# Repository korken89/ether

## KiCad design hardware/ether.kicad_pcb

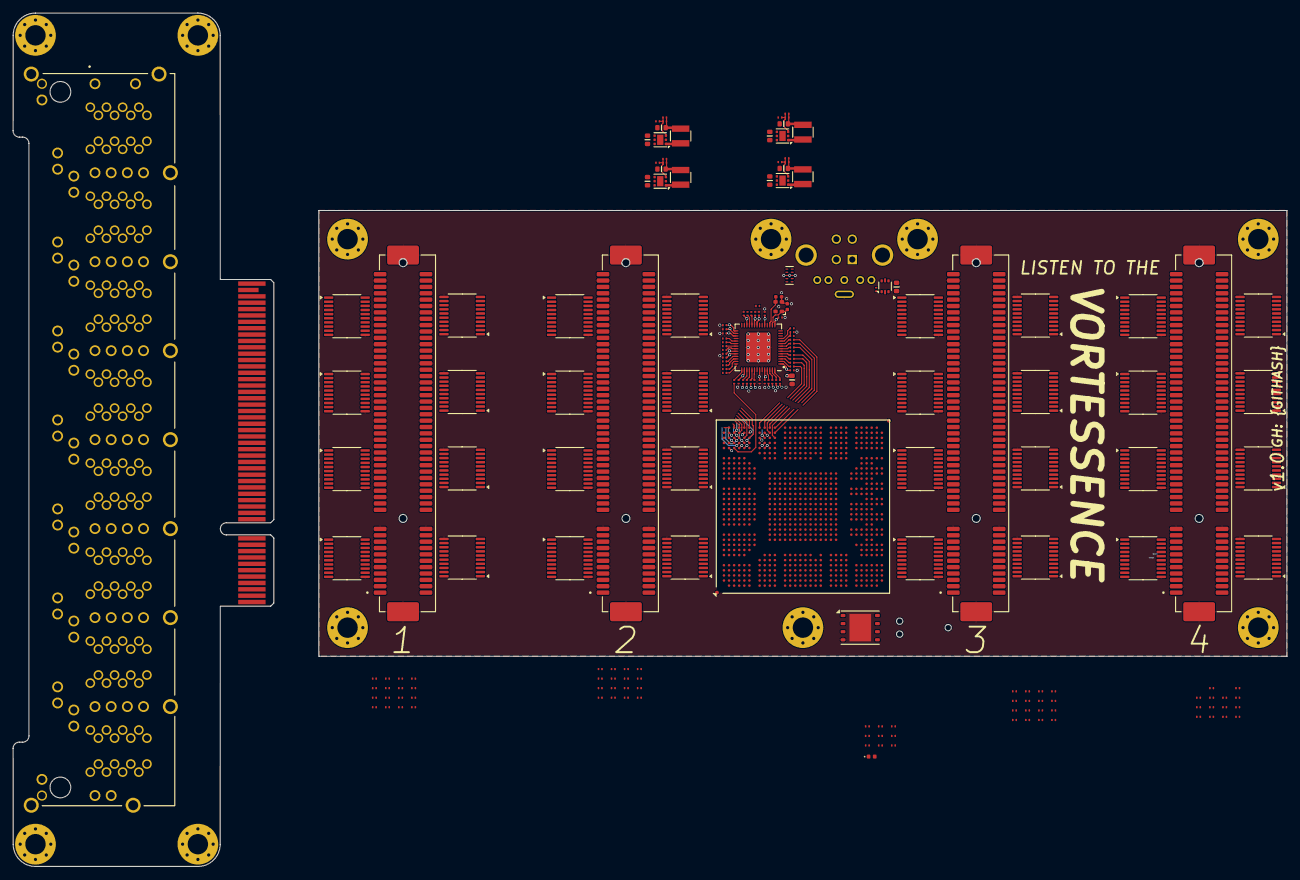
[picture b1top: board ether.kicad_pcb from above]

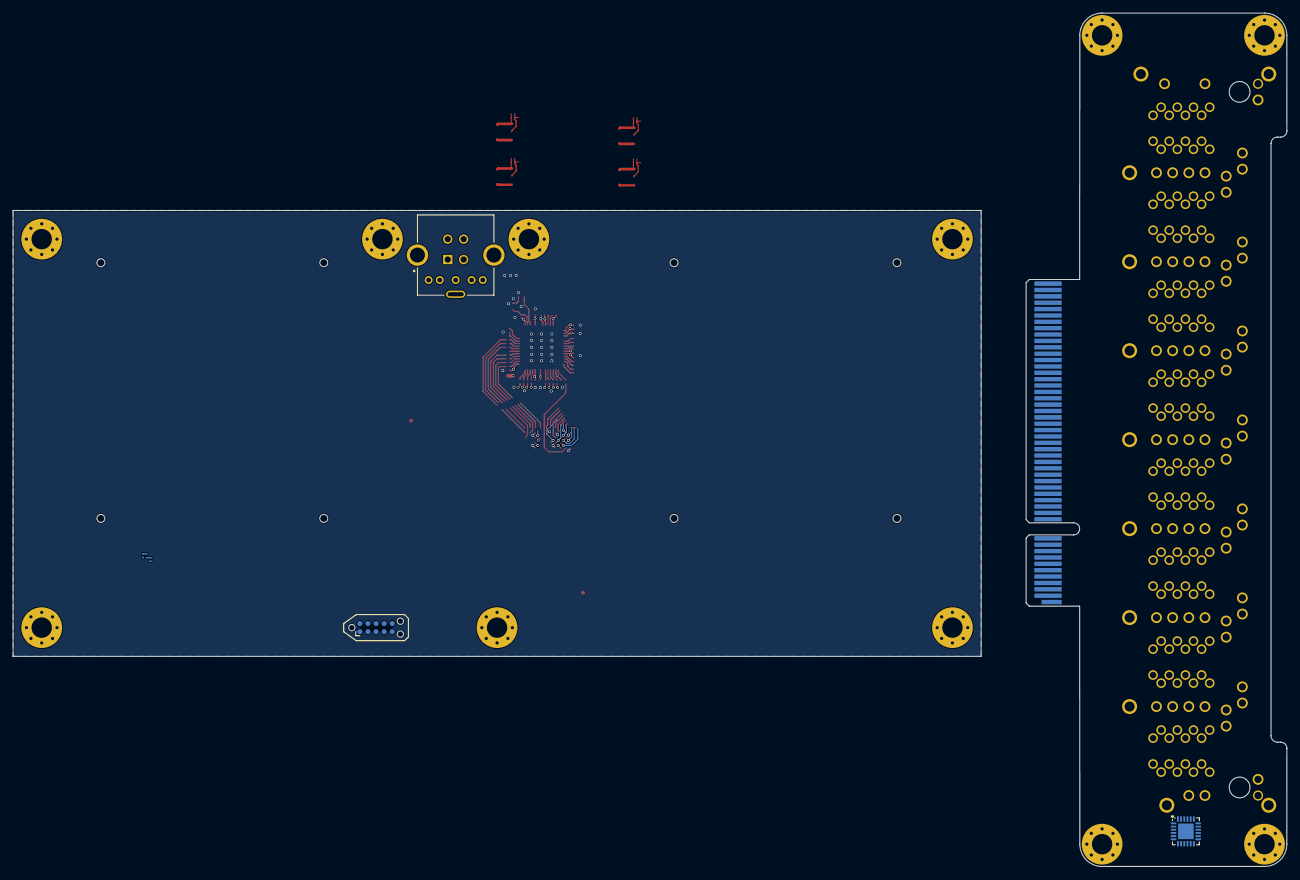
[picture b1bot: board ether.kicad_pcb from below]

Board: 6 copper layers, 200.0 x 134.0 mm, 205 parts (5 on the bottom side), 373 nets.

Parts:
C101, C102, C103, C104, C105, C106, C107, C108, C109, C110, C111, C112, C113, C114, C117, C118, C119, C120, C122, C301, C302, C303, C304, C305, C306, C307, C308, C309, C310, C311, C312, C313, C314, C315, C316, C401, C402, C403, C404, C405, C406, C407, C408, C409, C410, C411, C412, C413, C414, C415, C416, C501, C502, C503, C504, C505, C506, C507, C508, C509, C510, C511, C512, C513, C514, C515, C516, C601, C602, C603, C604, C605, C606, C607, C608, C609, C610, C611, C612, C613, C614, C615, C616: 0.1u; C_0201
C115, C116: 10p; C_0402
C121, C201, C202, C203, C204: 4.7u; C_0603
C206, C207, C208, C209: 22p; C_0201
C211, C212, C213, C214: 22u; C_0603
D101: LED_Small; LED_0402_1005Metric
FB101: FerriteBead_Small; R_0603
H101, H102, H103, H104, H105, H106, H107: MountingHole_Pad; MountingHole_3.2mm_M3_Pad_Via
J101: TC2050; Tag-Connect_TC2050-IDC-NL_2x05_P1.27mm_Vertical
J102: GSB422137EU; AMPHENOL_GSB422137EU
J301, J401, J501, J601: 10061913-102PLF; AMPHENOL_10061913-102PLF
J301#2: SS-74500-022; BEL_SS-74500-022
L201, L202, L203, L204: 2.2u; L_Abracon_ASPI-3012S
R101: 1.6k; R_0201
R102, R103, R104, R133, R136: 10k; R_0201
R105, R106, R107, R108, R109, R110, R111, R112, R113, R114, R115, R116, R117, R118, R119, R120, R121, R122, R123, R124, R125, R126, R127, R128: 33; R_0201
R129, R130, R131, R132, R134: 1k; R_0201
R135: 0; R_0201
R201, R202, R203, R204, R205, R206, R207, R208: R_0201
U101: ECP5U_85_CABGA756; Lattice_caBGA-756_27.0x27.0mm_Layout32x32_P0.8mm
U102: PUSB3FR4Z; DFN-10-1.0x2.5mm_P0.5mm
U103: FT600Q; QFN-56-1EP_7x7mm_P0.4mm_EP5.7x5.7mm_FT600
U104: TCA9535RTWR; WQFN-24-1EP_4x4mm_P0.5mm_EP2.45x2.45mm
U105: W25Q128JVP; WSON-8-1EP_6x5mm_P1.27mm_EP3.4x4.3mm
U108: USBLC6-2P6; SOT-666
U201, U202, U203, U204: TPS62290; WSON-6-1EP_2x2mm_P0.65mm_EP1x1.6mm
U301, U303, U305, U307, U309, U310, U311, U312, U401, U403, U405, U407, U409, U410, U411, U412, U501, U503, U505, U507, U509, U510, U511, U512, U601, U603, U605, U607, U609, U610, U611, U612: TXB0108DQSR; TSSOP-20_4.4x6.5mm_P0.65mm
Y101: 30 MHz; Crystal_4Pin_2.0x1.6mm

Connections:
+1V1: C206.2, C211.1, L201.2, R201.2, U101.AA12 (VCC[36]), U101.AA13 (VCC[36]), U101.AA14 (VCC[36]), U101.AA15 (VCC[36]), U101.AA16 (VCC[36]), U101.AA17 (VCC[36]), U101.AA18 (VCC[36]), U101.AA19 (VCC[36]), U101.AA20 (VCC[36]), U101.AA21 (VCC[36]), U101.M12 (VCC[36]), U101.M13 (VCC[36]), U101.M14 (VCC[36]), U101.M15 (VCC[36]), U101.M16 (VCC[36]), U101.M17 (VCC[36]), U101.M18 (VCC[36]), U101.M19 (VCC[36]), U101.M20 (VCC[36]), U101.M21 (VCC[36]), U101.N12 (VCC[36]), U101.N21 (VCC[36]), U101.P12 (VCC[36]), U101.P21 (VCC[36]), U101.R12 (VCC[36]), U101.R21 (VCC[36]), U101.T12 (VCC[36]), U101.T21 (VCC[36]), U101.U12 (VCC[36]), U101.U21 (VCC[36]), U101.V12 (VCC[36]), U101.V21 (VCC[36]), U101.W12 (VCC[36]), U101.W21 (VCC[36]), U101.Y12 (VCC[36]), U101.Y21 (VCC[36])
+1V5: C301.1, C302.1, C303.1, C304.1, C305.1, C306.1, C307.1, C308.1, C401.1, C402.1, C403.1, C404.1, C405.1, C406.1, C407.1, C408.1, C501.1, C502.1, C503.1, C504.1, C505.1, C506.1, C507.1, C508.1, C601.1, C602.1, C603.1, C604.1, C605.1, C606.1, C607.1, C608.1, U301.2 (V_{CCA}), U303.2 (V_{CCA}), U305.2 (V_{CCA}), U307.2 (V_{CCA}), U309.2 (V_{CCA}), U310.2 (V_{CCA}), U311.2 (V_{CCA}), U312.2 (V_{CCA}), U401.2 (V_{CCA}), U403.2 (V_{CCA}), U405.2 (V_{CCA}), U407.2 (V_{CCA}), U409.2 (V_{CCA}), U410.2 (V_{CCA}), U411.2 (V_{CCA}), U412.2 (V_{CCA}), U501.2 (V_{CCA}), U503.2 (V_{CCA}), U505.2 (V_{CCA}), U507.2 (V_{CCA}), U509.2 (V_{CCA}), U510.2 (V_{CCA}), U511.2 (V_{CCA}), U512.2 (V_{CCA}), U601.2 (V_{CCA}), U603.2 (V_{CCA}), U605.2 (V_{CCA}), U607.2 (V_{CCA}), U609.2 (V_{CCA}), U610.2 (V_{CCA}), U611.2 (V_{CCA}), U612.2 (V_{CCA})
+2V5: C208.2, C213.1, L203.2, R205.2, U101.AC11 (VCCAUX[8]), U101.AC22 (VCCAUX[8]), U101.K13 (VCCAUX[8]), U101.K20 (VCCAUX[8]), U101.N10 (VCCAUX[8]), U101.N23 (VCCAUX[8]), U101.Y10 (VCCAUX[8]), U101.Y23 (VCCAUX[8])
+3V3: C102.1, C103.1, C105.1, C109.1, C112.1, C113.1, C119.1, C122.1, C209.2, C214.1, J101.1, J301.B48, J401.B48, J501.B48, J601.B48, L204.2, R102.1, R103.1, R104.1, R129.1, R130.1, R131.1, R132.1, R133.1, R136.1, R207.2, U101.D28 (PR11B/-/URC_GPLL0C_IN/HS/RDQ17), U101.F31 (PR23A/+/HS/RDQ29), U101.J29 (PR32C/+/RDQ29), U101.N26 (PR44B/-/PCLKC2_1/HS/RDQ41), U101.N30 (PR41A/+/GR_PCLK2_1/HS/RDQS41), U103.15 (VCC33[3]), U103.19 (VCC33), U103.22 (VDDA), U103.30 (VCC33), U103.38 (VCCIO[3]), U103.44 (VCCIO), U103.52 (VCCIO), U105.8 (VCC)
+5V: C106.1, C201.1, C202.1, C203.1, C204.1, FB101.2, R135.2, U103.29 (VBUS), U201.4 (EN), U201.5 (VIN), U202.4 (EN), U202.5 (VIN), U203.4 (EN), U203.5 (VIN), U204.4 (EN), U204.5 (VIN)
/CFG_1: R130.2, U101.AL4 (CFG_1)
/DONE: D101.1 (K), U101.AJ4 (DONE)
/D_C_N: J102.2 (D-), U108.6 (I/O1)
/D_C_P: J102.3 (D+), U108.4 (I/O2)
/D_N: U103.20 (DM), U108.1 (I/O1)
/D_P: U103.18 (DP), U108.3 (I/O2)
/FT_BE0: R105.2, U101.E32 (PR23B/-/HS/RDQ29)
/FT_BE1: R106.2, U101.F32 (PR23C/+/RDQ29)
/FT_CLKOUT: R112.2, U101.C28 (PR11A/+/URC_GPLL0T_IN/HS/RDQ17)
/FT_D0: R113.2, U101.K32 (PR29C/+/RDQ29)
/FT_D1: R114.2, U101.L32 (PR29D/-/RDQ29)
/FT_D2: R115.2, U101.L31 (PR32A/+/HS/RDQ29)
/FT_D3: R116.2, U101.L30 (PR32B/-/HS/RDQ29)
/FT_D4: R117.2, U101.H27 (PR35A/+/HS/RDQ41)
/FT_D5: R118.2, U101.K29 (PR32D/-/RDQ29)
/FT_D6: R119.2, U101.J26 (PR35C/+/VREF1_2/RDQ41)
/FT_D7: R120.2, U101.H28 (PR35B/-/HS/RDQ41)
/FT_D8: R121.2, U101.K27 (PR38A/+/HS/RDQ41)
/FT_D9: R122.2, U101.K26 (PR38B/-/HS/RDQ41)
/FT_D10: R123.2, U101.K28 (PR38C/+/RDQ41)
/FT_D11: R124.2, U101.L29 (PR38D/-/RDQ41)
/FT_D12: R125.2, U101.N29 (PR41B/-/HS/RDQSN41)
/FT_D13: R126.2, U101.L26 (PR41C/+/GR_PCLK2_0/RDQ41)
/FT_D14: R127.2, U101.L27 (PR41D/-/RDQ41)
/FT_D15: R128.2, U101.N27 (PR44A/+/PCLKT2_1/HS/RDQ41)
/FT_GPIO0: U101.D31 (PR17D/-/RDQ17), U103.12 (GPIO0)
/FT_GPIO1: U101.F30 (PR20A/+/HS/RDQ17), U103.13 (GPIO1)
/FT_P_BE0: R105.1, U103.2 (BE_0)
/FT_P_BE1: R106.1, U103.3 (BE_1)
/FT_P_CLKOUT: R112.1, U103.43 (CLK)
/FT_P_D0: R113.1, U103.33 (DATA_0)
/FT_P_D1: R114.1, U103.34 (DATA_1)
/FT_P_D2: R115.1, U103.35 (DATA_2)
/FT_P_D3: R116.1, U103.36 (DATA_3)
/FT_P_D4: R117.1, U103.39 (DATA_4)
/FT_P_D5: R118.1, U103.40 (DATA_5)
/FT_P_D6: R119.1, U103.41 (DATA_6)
/FT_P_D7: R120.1, U103.42 (DATA_7)
/FT_P_D8: R121.1, U103.45 (DATA_8)
/FT_P_D9: R122.1, U103.46 (DATA_9)
/FT_P_D10: R123.1, U103.47 (DATA_10)
/FT_P_D11: R124.1, U103.48 (DATA_11)
/FT_P_D12: R125.1, U103.53 (DATA_12)
/FT_P_D13: R126.1, U103.54 (DATA_13)
/FT_P_D14: R127.1, U103.55 (DATA_14)
/FT_P_D15: R128.1, U103.56 (DATA_15)
/FT_REF: R101.1, U103.21 (RREF)
/FT_WAKEUP: R102.2, U101.D32 (PR20D/-/RDQ17), U103.11 (WAKEUP_N)
/INITN: R133.2, U101.AG4 (INITN)
/Input Port 1/IO_C_0: J301.A1, U301.12 (B8)
/Input Port 1/IO_C_1: J301.A3, U301.13 (B7)
/Input Port 1/IO_C_2: J301.A4, U301.14 (B6)
/Input Port 1/IO_C_3: J301.A6, U301.15 (B5)
/Input Port 1/IO_C_4: J301.A7, U301.16 (B4)
/Input Port 1/IO_C_5: J301.A9, U301.17 (B3)
/Input Port 1/IO_C_6: J301.A10, U301.18 (B2)
/Input Port 1/IO_C_7: J301.A12, U301.20 (B1)
/Input Port 1/IO_C_8: J301.A13, U303.12 (B8)
/Input Port 1/IO_C_9: J301.A15, U303.13 (B7)
/Input Port 1/IO_C_10: J301.A16, U303.14 (B6)
/Input Port 1/IO_C_11: J301.A18, U303.15 (B5)
/Input Port 1/IO_C_12: J301.A19, U303.16 (B4)
/Input Port 1/IO_C_13: J301.A21, U303.17 (B3)
/Input Port 1/IO_C_14: J301.A22, U303.18 (B2)
/Input Port 1/IO_C_15: J301.A24, U303.20 (B1)
/Input Port 1/IO_C_16: J301.A25, U305.12 (B8)
/Input Port 1/IO_C_17: J301.A27, U305.13 (B7)
/Input Port 1/IO_C_18: J301.A28, U305.14 (B6)
/Input Port 1/IO_C_19: J301.A30, U305.15 (B5)
/Input Port 1/IO_C_20: J301.A31, U305.16 (B4)
/Input Port 1/IO_C_21: J301.A33, U305.17 (B3)
/Input Port 1/IO_C_22: J301.A34, U305.18 (B2)
/Input Port 1/IO_C_23: J301.A36, U305.20 (B1)
/Input Port 1/IO_C_24: J301.A37, U307.12 (B8)
/Input Port 1/IO_C_25: J301.A39, U307.13 (B7)
/Input Port 1/IO_C_26: J301.A40, U307.14 (B6)
/Input Port 1/IO_C_27: J301.A42, U307.15 (B5)
/Input Port 1/IO_C_28: J301.A43, U307.16 (B4)
/Input Port 1/IO_C_29: J301.A45, U307.17 (B3)
/Input Port 1/IO_C_30: J301.A46, U307.18 (B2)
/Input Port 1/IO_C_31: J301.A47, U307.20 (B1)
/Input Port 1/IO_C_32: J301.B1, U309.20 (B1)
/Input Port 1/IO_C_33: J301.B3, U309.18 (B2)
/Input Port 1/IO_C_34: J301.B4, U309.17 (B3)
/Input Port 1/IO_C_35: J301.B6, U309.16 (B4)
/Input Port 1/IO_C_36: J301.B7, U309.15 (B5)
/Input Port 1/IO_C_37: J301.B9, U309.14 (B6)
/Input Port 1/IO_C_38: J301.B10, U309.13 (B7)
/Input Port 1/IO_C_39: J301.B12, U309.12 (B8)
/Input Port 1/IO_C_40: J301.B13, U310.20 (B1)
/Input Port 1/IO_C_41: J301.B15, U310.18 (B2)
/Input Port 1/IO_C_42: J301.B16, U310.17 (B3)
/Input Port 1/IO_C_43: J301.B18, U310.16 (B4)
/Input Port 1/IO_C_44: J301.B19, U310.15 (B5)
/Input Port 1/IO_C_45: J301.B21, U310.14 (B6)
/Input Port 1/IO_C_46: J301.B22, U310.13 (B7)
/Input Port 1/IO_C_47: J301.B24, U310.12 (B8)
/Input Port 1/IO_C_48: J301.B25, U311.20 (B1)
/Input Port 1/IO_C_49: J301.B27, U311.18 (B2)
/Input Port 1/IO_C_50: J301.B28, U311.17 (B3)
/Input Port 1/IO_C_51: J301.B30, U311.16 (B4)
/Input Port 1/IO_C_52: J301.B31, U311.15 (B5)
/Input Port 1/IO_C_53: J301.B33, U311.14 (B6)
/Input Port 1/IO_C_54: J301.B34, U311.13 (B7)
/Input Port 1/IO_C_55: J301.B36, U311.12 (B8)
/Input Port 1/IO_C_56: J301.B37, U312.20 (B1)
/Input Port 1/IO_C_57: J301.B39, U312.18 (B2)
/Input Port 1/IO_C_58: J301.B40, U312.17 (B3)
/Input Port 1/IO_C_59: J301.B42, U312.16 (B4)
/Input Port 1/IO_C_60: J301.B43, U312.15 (B5)
/Input Port 1/IO_C_61: J301.B45, U312.14 (B6)
/Input Port 1/IO_C_62: J301.B46, U312.13 (B7)
/Input Port 1/IO_C_63: J301.B47, U312.12 (B8)
/Input Port 1/OE: U301.10 (OE), U303.10 (OE), U305.10 (OE), U307.10 (OE), U309.10 (OE), U310.10 (OE), U311.10 (OE), U312.10 (OE)
/Input Port 2/IO_C_0: J401.A1, U401.12 (B8)
/Input Port 2/IO_C_1: J401.A3, U401.13 (B7)
/Input Port 2/IO_C_2: J401.A4, U401.14 (B6)
/Input Port 2/IO_C_3: J401.A6, U401.15 (B5)
/Input Port 2/IO_C_4: J401.A7, U401.16 (B4)
/Input Port 2/IO_C_5: J401.A9, U401.17 (B3)
/Input Port 2/IO_C_6: J401.A10, U401.18 (B2)
/Input Port 2/IO_C_7: J401.A12, U401.20 (B1)
/Input Port 2/IO_C_8: J401.A13, U403.12 (B8)
/Input Port 2/IO_C_9: J401.A15, U403.13 (B7)
/Input Port 2/IO_C_10: J401.A16, U403.14 (B6)
/Input Port 2/IO_C_11: J401.A18, U403.15 (B5)
/Input Port 2/IO_C_12: J401.A19, U403.16 (B4)
/Input Port 2/IO_C_13: J401.A21, U403.17 (B3)
/Input Port 2/IO_C_14: J401.A22, U403.18 (B2)
/Input Port 2/IO_C_15: J401.A24, U403.20 (B1)
/Input Port 2/IO_C_16: J401.A25, U405.12 (B8)
/Input Port 2/IO_C_17: J401.A27, U405.13 (B7)
/Input Port 2/IO_C_18: J401.A28, U405.14 (B6)
/Input Port 2/IO_C_19: J401.A30, U405.15 (B5)
/Input Port 2/IO_C_20: J401.A31, U405.16 (B4)
/Input Port 2/IO_C_21: J401.A33, U405.17 (B3)
/Input Port 2/IO_C_22: J401.A34, U405.18 (B2)
/Input Port 2/IO_C_23: J401.A36, U405.20 (B1)
/Input Port 2/IO_C_24: J401.A37, U407.12 (B8)
/Input Port 2/IO_C_25: J401.A39, U407.13 (B7)
/Input Port 2/IO_C_26: J401.A40, U407.14 (B6)
/Input Port 2/IO_C_27: J401.A42, U407.15 (B5)
/Input Port 2/IO_C_28: J401.A43, U407.16 (B4)
/Input Port 2/IO_C_29: J401.A45, U407.17 (B3)
/Input Port 2/IO_C_30: J401.A46, U407.18 (B2)
/Input Port 2/IO_C_31: J401.A47, U407.20 (B1)
/Input Port 2/IO_C_32: J401.B1, U409.20 (B1)
/Input Port 2/IO_C_33: J401.B3, U409.18 (B2)
/Input Port 2/IO_C_34: J401.B4, U409.17 (B3)
/Input Port 2/IO_C_35: J401.B6, U409.16 (B4)
/Input Port 2/IO_C_36: J401.B7, U409.15 (B5)
/Input Port 2/IO_C_37: J401.B9, U409.14 (B6)
/Input Port 2/IO_C_38: J401.B10, U409.13 (B7)
/Input Port 2/IO_C_39: J401.B12, U409.12 (B8)
/Input Port 2/IO_C_40: J401.B13, U410.20 (B1)
/Input Port 2/IO_C_41: J401.B15, U410.18 (B2)
/Input Port 2/IO_C_42: J401.B16, U410.17 (B3)
/Input Port 2/IO_C_43: J401.B18, U410.16 (B4)
/Input Port 2/IO_C_44: J401.B19, U410.15 (B5)
/Input Port 2/IO_C_45: J401.B21, U410.14 (B6)
/Input Port 2/IO_C_46: J401.B22, U410.13 (B7)
/Input Port 2/IO_C_47: J401.B24, U410.12 (B8)
/Input Port 2/IO_C_48: J401.B25, U411.20 (B1)
/Input Port 2/IO_C_49: J401.B27, U411.18 (B2)
/Input Port 2/IO_C_50: J401.B28, U411.17 (B3)
/Input Port 2/IO_C_51: J401.B30, U411.16 (B4)
/Input Port 2/IO_C_52: J401.B31, U411.15 (B5)
/Input Port 2/IO_C_53: J401.B33, U411.14 (B6)
/Input Port 2/IO_C_54: J401.B34, U411.13 (B7)
/Input Port 2/IO_C_55: J401.B36, U411.12 (B8)
/Input Port 2/IO_C_56: J401.B37, U412.20 (B1)
/Input Port 2/IO_C_57: J401.B39, U412.18 (B2)
/Input Port 2/IO_C_58: J401.B40, U412.17 (B3)
/Input Port 2/IO_C_59: J401.B42, U412.16 (B4)
/Input Port 2/IO_C_60: J401.B43, U412.15 (B5)
/Input Port 2/IO_C_61: J401.B45, U412.14 (B6)
/Input Port 2/IO_C_62: J401.B46, U412.13 (B7)
/Input Port 2/IO_C_63: J401.B47, U412.12 (B8)
/Input Port 2/OE: U401.10 (OE), U403.10 (OE), U405.10 (OE), U407.10 (OE), U409.10 (OE), U410.10 (OE), U411.10 (OE), U412.10 (OE)
/Input Port 3/IO_C_0: J501.A1, U501.12 (B8)
/Input Port 3/IO_C_1: J501.A3, U501.13 (B7)
/Input Port 3/IO_C_2: J501.A4, U501.14 (B6)
/Input Port 3/IO_C_3: J501.A6, U501.15 (B5)
/Input Port 3/IO_C_4: J501.A7, U501.16 (B4)
/Input Port 3/IO_C_5: J501.A9, U501.17 (B3)
/Input Port 3/IO_C_6: J501.A10, U501.18 (B2)
/Input Port 3/IO_C_7: J501.A12, U501.20 (B1)
/Input Port 3/IO_C_8: J501.A13, U503.12 (B8)
/Input Port 3/IO_C_9: J501.A15, U503.13 (B7)
/Input Port 3/IO_C_10: J501.A16, U503.14 (B6)
/Input Port 3/IO_C_11: J501.A18, U503.15 (B5)
/Input Port 3/IO_C_12: J501.A19, U503.16 (B4)
/Input Port 3/IO_C_13: J501.A21, U503.17 (B3)
/Input Port 3/IO_C_14: J501.A22, U503.18 (B2)
/Input Port 3/IO_C_15: J501.A24, U503.20 (B1)
/Input Port 3/IO_C_16: J501.A25, U505.12 (B8)
/Input Port 3/IO_C_17: J501.A27, U505.13 (B7)
/Input Port 3/IO_C_18: J501.A28, U505.14 (B6)
/Input Port 3/IO_C_19: J501.A30, U505.15 (B5)
/Input Port 3/IO_C_20: J501.A31, U505.16 (B4)
/Input Port 3/IO_C_21: J501.A33, U505.17 (B3)
/Input Port 3/IO_C_22: J501.A34, U505.18 (B2)
/Input Port 3/IO_C_23: J501.A36, U505.20 (B1)
/Input Port 3/IO_C_24: J501.A37, U507.12 (B8)
/Input Port 3/IO_C_25: J501.A39, U507.13 (B7)
/Input Port 3/IO_C_26: J501.A40, U507.14 (B6)
/Input Port 3/IO_C_27: J501.A42, U507.15 (B5)
/Input Port 3/IO_C_28: J501.A43, U507.16 (B4)
/Input Port 3/IO_C_29: J501.A45, U507.17 (B3)
/Input Port 3/IO_C_30: J501.A46, U507.18 (B2)
/Input Port 3/IO_C_31: J501.A47, U507.20 (B1)
/Input Port 3/IO_C_32: J501.B1, U509.20 (B1)
/Input Port 3/IO_C_33: J501.B3, U509.18 (B2)
/Input Port 3/IO_C_34: J501.B4, U509.17 (B3)
/Input Port 3/IO_C_35: J501.B6, U509.16 (B4)
/Input Port 3/IO_C_36: J501.B7, U509.15 (B5)
/Input Port 3/IO_C_37: J501.B9, U509.14 (B6)
/Input Port 3/IO_C_38: J501.B10, U509.13 (B7)
/Input Port 3/IO_C_39: J501.B12, U509.12 (B8)
/Input Port 3/IO_C_40: J501.B13, U510.20 (B1)
/Input Port 3/IO_C_41: J501.B15, U510.18 (B2)
/Input Port 3/IO_C_42: J501.B16, U510.17 (B3)
/Input Port 3/IO_C_43: J501.B18, U510.16 (B4)
/Input Port 3/IO_C_44: J501.B19, U510.15 (B5)
/Input Port 3/IO_C_45: J501.B21, U510.14 (B6)
/Input Port 3/IO_C_46: J501.B22, U510.13 (B7)
/Input Port 3/IO_C_47: J501.B24, U510.12 (B8)
/Input Port 3/IO_C_48: J501.B25, U511.20 (B1)
/Input Port 3/IO_C_49: J501.B27, U511.18 (B2)
/Input Port 3/IO_C_50: J501.B28, U511.17 (B3)
/Input Port 3/IO_C_51: J501.B30, U511.16 (B4)
/Input Port 3/IO_C_52: J501.B31, U511.15 (B5)
/Input Port 3/IO_C_53: J501.B33, U511.14 (B6)
/Input Port 3/IO_C_54: J501.B34, U511.13 (B7)
/Input Port 3/IO_C_55: J501.B36, U511.12 (B8)
/Input Port 3/IO_C_56: J501.B37, U512.20 (B1)
/Input Port 3/IO_C_57: J501.B39, U512.18 (B2)
/Input Port 3/IO_C_58: J501.B40, U512.17 (B3)
/Input Port 3/IO_C_59: J501.B42, U512.16 (B4)
/Input Port 3/IO_C_60: J501.B43, U512.15 (B5)
/Input Port 3/IO_C_61: J501.B45, U512.14 (B6)
/Input Port 3/IO_C_62: J501.B46, U512.13 (B7)
/Input Port 3/IO_C_63: J501.B47, U512.12 (B8)
/Input Port 3/OE: U501.10 (OE), U503.10 (OE), U505.10 (OE), U507.10 (OE), U509.10 (OE), U510.10 (OE), U511.10 (OE), U512.10 (OE)
/Input Port 4/IO_C_0: J601.A1, U601.12 (B8)
/Input Port 4/IO_C_1: J601.A3, U601.13 (B7)
/Input Port 4/IO_C_2: J601.A4, U601.14 (B6)
/Input Port 4/IO_C_3: J601.A6, U601.15 (B5)
/Input Port 4/IO_C_4: J601.A7, U601.16 (B4)
/Input Port 4/IO_C_5: J601.A9, U601.17 (B3)
/Input Port 4/IO_C_6: J601.A10, U601.18 (B2)
/Input Port 4/IO_C_7: J601.A12, U601.20 (B1)
/Input Port 4/IO_C_8: J601.A13, U603.12 (B8)
/Input Port 4/IO_C_9: J601.A15, U603.13 (B7)
/Input Port 4/IO_C_10: J601.A16, U603.14 (B6)
/Input Port 4/IO_C_11: J601.A18, U603.15 (B5)
/Input Port 4/IO_C_12: J601.A19, U603.16 (B4)
/Input Port 4/IO_C_13: J601.A21, U603.17 (B3)
/Input Port 4/IO_C_14: J601.A22, U603.18 (B2)
/Input Port 4/IO_C_15: J601.A24, U603.20 (B1)
/Input Port 4/IO_C_16: J601.A25, U605.12 (B8)
/Input Port 4/IO_C_17: J601.A27, U605.13 (B7)
/Input Port 4/IO_C_18: J601.A28, U605.14 (B6)
/Input Port 4/IO_C_19: J601.A30, U605.15 (B5)
/Input Port 4/IO_C_20: J601.A31, U605.16 (B4)
/Input Port 4/IO_C_21: J601.A33, U605.17 (B3)
/Input Port 4/IO_C_22: J601.A34, U605.18 (B2)
/Input Port 4/IO_C_23: J601.A36, U605.20 (B1)
/Input Port 4/IO_C_24: J601.A37, U607.12 (B8)
/Input Port 4/IO_C_25: J601.A39, U607.13 (B7)
/Input Port 4/IO_C_26: J601.A40, U607.14 (B6)
/Input Port 4/IO_C_27: J601.A42, U607.15 (B5)
/Input Port 4/IO_C_28: J601.A43, U607.16 (B4)
/Input Port 4/IO_C_29: J601.A45, U607.17 (B3)
/Input Port 4/IO_C_30: J601.A46, U607.18 (B2)
/Input Port 4/IO_C_31: J601.A47, U607.20 (B1)
/Input Port 4/IO_C_32: J601.B1, U609.20 (B1)
/Input Port 4/IO_C_33: J601.B3, U609.18 (B2)
/Input Port 4/IO_C_34: J601.B4, U609.17 (B3)
/Input Port 4/IO_C_35: J601.B6, U609.16 (B4)
/Input Port 4/IO_C_36: J601.B7, U609.15 (B5)
/Input Port 4/IO_C_37: J601.B9, U609.14 (B6)
/Input Port 4/IO_C_38: J601.B10, U609.13 (B7)
/Input Port 4/IO_C_39: J601.B12, U609.12 (B8)
/Input Port 4/IO_C_40: J601.B13, U610.20 (B1)
/Input Port 4/IO_C_41: J601.B15, U610.18 (B2)
/Input Port 4/IO_C_42: J601.B16, U610.17 (B3)
/Input Port 4/IO_C_43: J601.B18, U610.16 (B4)
/Input Port 4/IO_C_44: J601.B19, U610.15 (B5)
/Input Port 4/IO_C_45: J601.B21, U610.14 (B6)
/Input Port 4/IO_C_46: J601.B22, U610.13 (B7)
/Input Port 4/IO_C_47: J601.B24, U610.12 (B8)
/Input Port 4/IO_C_48: J601.B25, U611.20 (B1)
/Input Port 4/IO_C_49: J601.B27, U611.18 (B2)
/Input Port 4/IO_C_50: J601.B28, U611.17 (B3)
/Input Port 4/IO_C_51: J601.B30, U611.16 (B4)
/Input Port 4/IO_C_52: J601.B31, U611.15 (B5)
/Input Port 4/IO_C_53: J601.B33, U611.14 (B6)
/Input Port 4/IO_C_54: J601.B34, U611.13 (B7)
/Input Port 4/IO_C_55: J601.B36, U611.12 (B8)
/Input Port 4/IO_C_56: J601.B37, U612.20 (B1)
/Input Port 4/IO_C_57: J601.B39, U612.18 (B2)
/Input Port 4/IO_C_58: J601.B40, U612.17 (B3)
/Input Port 4/IO_C_59: J601.B42, U612.16 (B4)
/Input Port 4/IO_C_60: J601.B43, U612.15 (B5)
/Input Port 4/IO_C_61: J601.B45, U612.14 (B6)
/Input Port 4/IO_C_62: J601.B46, U612.13 (B7)
/Input Port 4/IO_C_63: J601.B47, U612.12 (B8)
/Input Port 4/OE: U601.10 (OE), U603.10 (OE), U605.10 (OE), U607.10 (OE), U609.10 (OE), U610.10 (OE), U611.10 (OE), U612.10 (OE)
/PORT1: U101.A2 (PT6A/+), U101.A3 (PT6B/-), U101.A4 (PT9A/+), U101.A5 (PT9B/-), U101.A7 (PT13B/-), U101.A8 (PT20B/-), U101.A9 (PT24B/-), U101.A10 (PT31B/-), U101.A11 (PT38B/-), U101.A13 (PT42B/-), U101.A14 (PT49B/-), U101.A15 (PT54B/-), U101.A16 (PT60B/-/GR_PCLK0_0), U101.A17 (PT63A/+/PCLKT0_1), U101.B3 (PT4A/+/ULC_GPLL1T_IN), U101.B4 (PT4B/-/ULC_GPLL1C_IN), U101.B7 (PT13A/+), U101.B8 (PT20A/+), U101.B10 (PT31A/+), U101.B11 (PT38A/+), U101.B14 (PT49A/+), U101.B16 (PT60A/+/GR_PCLK0_1), U101.B17 (PT63B/-/PCLKC0_1), U101.C7 (PT11B/-), U101.C8 (PT18B/-), U101.C9 (PT24A/+), U101.C10 (PT29B/-), U101.C11 (PT36B/-), U101.C13 (PT42A/+), U101.C14 (PT47B/-), U101.C15 (PT54A/+), U101.C16 (PT58B/-), U101.C17 (PT65A/+/PCLKT0_0), U101.D7 (PT11A/+), U101.D8 (PT18A/+), U101.D9 (PT22B/-), U101.D10 (PT29A/+), U101.D11 (PT36A/+), U101.D13 (PT40B/-), U101.D14 (PT47A/+), U101.D15 (PT51B/-), U101.D16 (PT58A/+), U101.D17 (PT65B/-/PCLKC0_0), U101.E8 (PT15B/-), U101.E10 (PT27B/-), U101.E11 (PT33B/-), U101.E14 (PT45B/-), U101.E16 (PT56B/-), U101.F8 (PT15A/+), U101.F9 (PT22A/+), U101.F10 (PT27A/+), U101.F11 (PT33A/+), U101.F13 (PT40A/+), U101.F14 (PT45A/+), U101.F15 (PT51A/+), U101.F16 (PT56A/+)
/PORT3: U101.A18 (PT71A/+/PCLKT1_0), U101.A19 (PT76A/+), U101.A20 (PT83A/+), U101.A22 (PT87A/+), U101.A23 (PT94A/+), U101.A24 (PT101A/+), U101.A25 (PT105A/+), U101.A26 (PT112A/+), U101.A28 (PT116A/+), U101.A29 (PT116B/-), U101.A30 (PT119A/+), U101.A31 (PT119B/-), U101.B19 (PT76B/-), U101.B22 (PT87B/-), U101.B23 (PT94B/-), U101.B25 (PT105B/-), U101.B26 (PT112B/-), U101.B29 (PT121A/+/URC_GPLL1T_IN), U101.B30 (PT121B/-/URC_GPLL1C_IN), U101.C18 (PT71B/-/PCLKC1_0), U101.C19 (PT78A/+), U101.C20 (PT83B/-), U101.C22 (PT89A/+), U101.C23 (PT96A/+), U101.C24 (PT101B/-), U101.C25 (PT107A/+), U101.C26 (PT114A/+), U101.D18 (PT74A/+/GR_PCLK1_0), U101.D19 (PT78B/-), U101.D20 (PT85A/+), U101.D22 (PT89B/-), U101.D23 (PT96B/-), U101.D24 (PT103A/+), U101.D25 (PT107B/-), U101.D26 (PT114B/-), U101.E17 (PT69A/+/PCLKT1_1), U101.E19 (PT80A/+), U101.E22 (PT92A/+), U101.E23 (PT98A/+), U101.E25 (PT110A/+), U101.F17 (PT69B/-/PCLKC1_1), U101.F18 (PT74B/-/GR_PCLK1_1), U101.F19 (PT80B/-), U101.F20 (PT85B/-), U101.F22 (PT92B/-), U101.F23 (PT98B/-), U101.F24 (PT103B/-), U101.F25 (PT110B/-)
/PORT4: U101.AB26 (PR74C/+/RDQ77), U101.AB27 (PR77B/-/HS/RDQSN77), U101.AB28 (PR77A/+/HS/RDQS77), U101.AB29 (PR83B/-/HS/RDQ89), U101.AB30 (PR83A/+/HS/RDQ89), U101.AB31 (PR89B/-/HS/RDQSN89), U101.AB32 (PR92A/+/HS/RDQ89), U101.AC26 (PR77C/+/RDQ77), U101.AC27 (PR74D/-/RDQ77), U101.AC28 (PR83C/+/RDQ89), U101.AC30 (PR89A/+/HS/RDQS89), U101.AC31 (PR89C/+/RDQ89), U101.AC32 (PR92B/-/HS/RDQ89), U101.AD26 (PR77D/-/RDQ77), U101.AD27 (PR80A/+/HS/RDQ77), U101.AD29 (PR83D/-/RDQ89), U101.AD30 (PR86C/+/RDQ89), U101.AD32 (PR92C/+/LRC_GPLL0T_IN/RDQ89), U101.AE27 (PR80B/-/HS/RDQ77), U101.AE28 (PR80C/+/RDQ77), U101.AE29 (PR80D/-/RDQ77), U101.AE30 (PR86D/-/RDQ89), U101.AE31 (PR89D/-/RDQ89), U101.AE32 (PR92D/-/LRC_GPLL0C_IN/RDQ89), U101.N32 (PR62A/+/HS/RDQ65), U101.P28 (PR47A/+/PCLKT3_1/HS/RDQ53), U101.P29 (PR47B/-/PCLKC3_1/HS/RDQ53), U101.P30 (PR59B/-/HS/RDQ65), U101.P31 (PR59A/+/HS/RDQ65), U101.P32 (PR62B/-/HS/RDQ65), U101.R26 (PR47C/+/PCLKT3_0/RDQ53), U101.R27 (PR50A/+/GR_PCLK3_0/HS/RDQ53), U101.R29 (PR53A/+/HS/RDQS53), U101.R30 (PR59C/+/RDQ65), U101.R32 (PR65A/+/HS/RDQS65), U101.T26 (PR47D/-/PCLKC3_0/RDQ53), U101.T27 (PR50B/-/HS/RDQ53), U101.T28 (PR53B/-/HS/RDQSN53), U101.T29 (PR53C/+/RDQ53), U101.T30 (PR59D/-/RDQ65), U101.T31 (PR65B/-/HS/RDQSN65), U101.T32 (PR68A/+/HS/RDQ65), U101.U26 (PR50D/-/RDQ53), U101.U27 (PR50C/+/GR_PCLK3_1/RDQ53), U101.U28 (PR53D/-/RDQ53), U101.U29 (PR56A/+/HS/RDQ53), U101.U30 (PR62D/-/RDQ65), U101.U31 (PR62C/+/RDQ65), U101.U32 (PR68B/-/HS/RDQ65), U101.V26 (PR56D/-/RDQ53), U101.V27 (PR56C/+/RDQ53), U101.V29 (PR56B/-/VREF1_3/HS/RDQ53), U101.V32 (PR68C/+/RDQ65), U101.W28 (PR71D/-/RDQ77), U101.W29 (PR74B/-/HS/RDQ77), U101.W30 (PR65C/+/RDQ65), U101.W31 (PR86A/+/HS/RDQ89), U101.W32 (PR68D/-/RDQ65), U101.Y26 (PR71A/+/HS/RDQ77), U101.Y27 (PR71B/-/HS/RDQ77), U101.Y28 (PR71C/+/RDQ77), U101.Y29 (PR74A/+/HS/RDQ77), U101.Y30 (PR65D/-/RDQ65), U101.Y32 (PR86B/-/HS/RDQ89)
/PORT5: U101.AG28 (PB110A/+), U101.AG29 (PB110B/-), U101.AG30 (PB114B/-), U101.AG32 (PB119B/-), U101.AH28 (PB112B/-), U101.AH30 (PB114A/+), U101.AH32 (PB119A/+), U101.AJ28 (PB112A/+), U101.AJ29 (PB121A/+), U101.AJ30 (PB121B/-), U101.AJ31 (PB105B/-), U101.AJ32 (PB101B/-), U101.AK28 (PB98B/-), U101.AK29 (PB116A/+), U101.AK30 (PB116B/-), U101.AK31 (PB105A/+), U101.AK32 (PB101A/+), U101.AL28 (PB98A/+), U101.AL30 (PB103B/-), U101.AL32 (PB107B/-), U101.AM28 (PB96A/+), U101.AM29 (PB96B/-), U101.AM30 (PB103A/+), U101.AM31 (PB107A/+)
/PORT6: U101.AB1 (PL92A/+/HS/LDQ89), U101.AB2 (PL89B/-/HS/LDQSN89), U101.AB3 (PL83A/+/HS/LDQ89), U101.AB4 (PL83B/-/HS/LDQ89), U101.AB5 (PL77A/+/HS/LDQS77), U101.AB6 (PL77B/-/HS/LDQSN77), U101.AB7 (PL74C/+/LDQ77), U101.AC1 (PL92B/-/HS/LDQ89), U101.AC2 (PL89C/+/LDQ89), U101.AC3 (PL89A/+/HS/LDQS89), U101.AC5 (PL83C/+/LDQ89), U101.AC6 (PL74D/-/LDQ77), U101.AC7 (PL77C/+/LDQ77), U101.AD1 (PL92C/+/LLC_GPLL0T_IN/LDQ89), U101.AD3 (PL86C/+/LDQ89), U101.AD4 (PL83D/-/LDQ89), U101.AD6 (PL80A/+/HS/LDQ77), U101.AD7 (PL77D/-/LDQ77), U101.AE1 (PL92D/-/LLC_GPLL0C_IN/LDQ89), U101.AE2 (PL89D/-/LDQ89), U101.AE3 (PL86D/-/LDQ89), U101.AE4 (PL80D/-/LDQ77), U101.AE5 (PL80C/+/LDQ77), U101.AE6 (PL80B/-/HS/LDQ77), U101.N1 (PL62A/+/HS/LDQ65), U101.P1 (PL62B/-/HS/LDQ65), U101.P2 (PL59A/+/HS/LDQ65), U101.P3 (PL59B/-/HS/LDQ65), U101.P4 (PL47B/-/PCLKC6_1/HS/LDQ53), U101.P5 (PL47A/+/PCLKT6_1/HS/LDQ53), U101.R1 (PL65A/+/HS/LDQS65), U101.R3 (PL59C/+/LDQ65), U101.R4 (PL53A/+/HS/LDQS53), U101.R6 (PL50A/+/GR_PCLK6_0/HS/LDQ53), U101.R7 (PL47C/+/PCLKT6_0/LDQ53), U101.T1 (PL68A/+/HS/LDQ65), U101.T2 (PL65B/-/HS/LDQSN65), U101.T3 (PL59D/-/LDQ65), U101.T4 (PL53C/+/LDQ53), U101.T5 (PL53B/-/HS/LDQSN53), U101.T6 (PL50B/-/HS/LDQ53), U101.T7 (PL47D/-/PCLKC6_0/LDQ53), U101.U1 (PL68B/-/HS/LDQ65), U101.U2 (PL62C/+/LDQ65), U101.U3 (PL62D/-/LDQ65), U101.U4 (PL56A/+/HS/LDQ53), U101.U5 (PL53D/-/LDQ53), U101.U6 (PL50C/+/GR_PCLK6_1/LDQ53), U101.U7 (PL50D/-/LDQ53), U101.V1 (PL68C/+/LDQ65), U101.V4 (PL56B/-/VREF1_6/HS/LDQ53), U101.V6 (PL56C/+/LDQ53), U101.V7 (PL56D/-/LDQ53), U101.W1 (PL68D/-/LDQ65), U101.W2 (PL86A/+/HS/LDQ89), U101.W3 (PL65C/+/LDQ65), U101.W4 (PL74B/-/HS/LDQ77), U101.W5 (PL71D/-/LDQ77), U101.Y1 (PL86B/-/HS/LDQ89), U101.Y3 (PL65D/-/LDQ65), U101.Y4 (PL74A/+/HS/LDQ77), U101.Y5 (PL71C/+/LDQ77), U101.Y6 (PL71B/-/HS/LDQ77), U101.Y7 (PL71A/+/HS/LDQ77)
/PORT7: U101.B1 (PL17A/+/HS/LDQS17), U101.C1 (PL20C/+/LDQ17), U101.C2 (PL17B/-/HS/LDQSN17), U101.C3 (PL11D/-/LDQ17), U101.C4 (PL11C/+/LDQ17), U101.C5 (PL11A/+/ULC_GPLL0T_IN/HS/LDQ17), U101.D1 (PL20D/-/LDQ17), U101.D2 (PL17D/-/LDQ17), U101.D3 (PL17C/+/LDQ17), U101.D4 (PL14A/+/HS/LDQ17), U101.D5 (PL11B/-/ULC_GPLL0C_IN/HS/LDQ17), U101.E1 (PL23B/-/HS/LDQ29), U101.E3 (PL20B/-/HS/LDQ17), U101.E4 (PL14B/-/HS/LDQ17), U101.F1 (PL23C/+/LDQ29), U101.F2 (PL23A/+/HS/LDQ29), U101.F3 (PL20A/+/HS/LDQ17), U101.F4 (PL14C/+/LDQ17), U101.F5 (PL14D/-/LDQ17), U101.H1 (PL23D/-/LDQ29), U101.H2 (PL26A/+/HS/LDQ29), U101.H3 (PL26B/-/HS/LDQ29), U101.H5 (PL35B/-/HS/LDQ41), U101.H6 (PL35A/+/HS/LDQ41), U101.J1 (PL29B/-/HS/LDQSN29), U101.J3 (PL26C/+/LDQ29), U101.J4 (PL32C/+/LDQ29), U101.J6 (PL35D/-/LDQ41), U101.J7 (PL35C/+/VREF1_7/LDQ41), U101.K1 (PL29C/+/LDQ29), U101.K2 (PL29A/+/HS/LDQS29), U101.K3 (PL26D/-/LDQ29), U101.K4 (PL32D/-/LDQ29), U101.K5 (PL38C/+/LDQ41), U101.K6 (PL38A/+/HS/LDQ41), U101.K7 (PL38B/-/HS/LDQ41), U101.L1 (PL29D/-/LDQ29), U101.L2 (PL32A/+/HS/LDQ29), U101.L3 (PL32B/-/HS/LDQ29), U101.L4 (PL38D/-/LDQ41), U101.L6 (PL41D/-/LDQ41), U101.L7 (PL41C/+/GR_PCLK7_0/LDQ41), U101.N3 (PL41A/+/GR_PCLK7_1/HS/LDQS41), U101.N4 (PL41B/-/HS/LDQSN41), U101.N6 (PL44A/+/PCLKT7_1/HS/LDQ41), U101.N7 (PL44B/-/PCLKC7_1/HS/LDQ41), U101.P6 (PL44C/+/PCLKT7_0/LDQ41), U101.P7 (PL44D/-/PCLKC7_0/LDQ41)
/PROGRAMN: R132.2, U101.AH4 (PROGRAMN)
/Power/FB_1V1: C206.1, R201.1, R202.2, U201.3 (FB)
/Power/FB_1V5: C207.1, R203.1, R204.2, U202.3 (FB)
/Power/FB_2V5: C208.1, R205.1, R206.2, U203.3 (FB)
/Power/FB_3V3: C209.1, R207.1, R208.2, U204.3 (FB)
/RX_N: J102.8 (STDB_SSRX-), U102.4, U102.7, U103.27 (RIDN)
/RX_P: J102.9 (STDB_SSRX+), U102.5, U102.6, U103.28 (RIDP)
/SPI_CLK: R129.2, U101.AM3 (CCLK/MCLK/SCK), U105.6 (CLK)
/SPI_CS: R136.2, U101.AJ3 (PB15A/+/HOLDN/DI/BUSY/CSSPIN/CEN), U105.1 (~CS)
/SPI_D2: U101.AM2 (PB9B/-/D2/IO2), U105.3 (IO2)
/SPI_D3: U101.AL1 (PB9A/+/D3/IO3), U105.7 (IO3)
/SPI_MISO: U101.AJ2 (PB11A/+/D1/MISO/IO1), U105.2 (DO(IO1))
/SPI_MOSI: U101.AK2 (PB11B/-/D0/MOSI/IO0), U105.5 (DI(IO0))
/TCK: J101.4, R134.1, U101.AK5 (TCK)
/TDI: J101.8, U101.AJ5 (TDI)
/TDO: J101.6, U101.AG5 (TDO)
/TMS: J101.2, U101.AM5 (TMS)
/TX_N: C117.1, J102.5 (STDB_SSTX-), U102.1, U102.10
/TX_P: C118.1, J102.6 (STDB_SSTX+), U102.2, U102.9
/TX_P_N: C117.2, U103.24 (TODN)
/TX_P_P: C118.2, U103.25 (TODP)
/VBUS_IN: C101.1, FB101.1, J102.1 (VBUS), U108.5 (VBUS)
/~FT_OE: R111.2, U101.K31 (PR29A/+/HS/RDQS29)
/~FT_P_OE: R111.1, U103.9 (OE_N)
/~FT_P_RD: R110.1, U103.8 (RD_N)
/~FT_P_RXF: R108.1, U103.5 (RXF_N)
/~FT_P_TXE: R107.1, U103.4 (TXE_N)
/~FT_P_WR: R109.1, U103.7 (WR_N)
/~FT_RD: R110.2, U101.K30 (PR26D/-/RDQ29)
/~FT_RESET: C110.1, R103.2, U101.C32 (PR20C/+/RDQ17), U103.10 (RESET_N)
/~FT_RXF: R108.2, U101.H30 (PR26B/-/HS/RDQ29)
/~FT_SIWU: R104.2, U101.E30 (PR20B/-/HS/RDQ17), U103.6 (SIWU_N)
/~FT_TXE: R107.2, U101.H32 (PR23D/-/RDQ29)
/~FT_WR: R109.2, U101.J30 (PR26C/+/RDQ29)
GND: C101.2, C102.2, C103.2, C104.2, C105.2, C106.2, C107.2, C108.2, C109.2, C110.2, C111.2, C112.2, C113.2, C114.2, C115.2, C116.2, C119.2, C120.2, C121.2, C122.2, C201.2, C202.2, C203.2, C204.2, C211.2, C212.2, C213.2, C214.2, C301.2, C302.2, C303.2, C304.2, C305.2, C306.2, C307.2, C308.2, C309.2, C310.2, C311.2, C312.2, C313.2, C314.2, C315.2, C316.2, C401.2, C402.2, C403.2, C404.2, C405.2, C406.2, C407.2, C408.2, C409.2, C410.2, C411.2, C412.2, C413.2, C414.2, C415.2, C416.2, C501.2, C502.2, C503.2, C504.2, C505.2, C506.2, C507.2, C508.2, C509.2, C510.2, C511.2, C512.2, C513.2, C514.2, C515.2, C516.2, C601.2, C602.2, C603.2, C604.2, C605.2, C606.2, C607.2, C608.2, C609.2, C610.2, C611.2, C612.2, C613.2, C614.2, C615.2, C616.2, H101.1, H102.1, H103.1, H104.1, H105.1, H106.1, H107.1, J101.3, J102.4 (GND), J102.7 (GND_DRAIN), J102.SH1 (SHIELD), J102.SH2 (SHIELD__1), J102.SH3 (SHIELD__2), J301.A2, J301.A5, J301.A8, J301.A11, J301.A14, J301.A17, J301.A20, J301.A23, J301.A26, J301.A29, J301.A32, J301.A35, J301.A38, J301.A41, J301.A44, J301.A48, J301.B2, J301.B5, J301.B8, J301.B11, J301.B14, J301.B17, J301.B20, J301.B23, J301.B26, J301.B29, J301.B32, J301.B35, J301.B38, J301.B41, J301.B44, J301.S1 (SHIELD), J301.S2 (SHIELD__1), J301#2.10_1, J301#2.10_2, J301#2.10_3, J301#2.10_4, J301#2.10_5, J301#2.10_6, J301#2.10_7, J301#2.10_8, J301#2.10_9, J301#2.10_10, J301#2.10_11, J301#2.10_12, J301#2.10_13, J301#2.10_14, J301#2.10_15, J301#2.10_16, J301#2.12_1, J301#2.12_2, J301#2.12_3, J301#2.12_4, J301#2.12_5, J301#2.12_6, J301#2.12_7, J301#2.12_8, J301#2.12_9, J301#2.12_10, J301#2.12_11, J301#2.12_12, J301#2.12_13, J301#2.12_14, J301#2.12_15, J301#2.12_16, J301#2.S1 (SHIELD), J301#2.S2 (SHIELD__1), J301#2.S3 (SHIELD__2), J301#2.S4 (SHIELD__3), J301#2.S5 (SHIELD__4), J301#2.S6 (SHIELD__5), J301#2.S7 (SHIELD__6), J301#2.S8 (SHIELD__7), J301#2.S9 (SHIELD__8), J301#2.S10 (SHIELD__9), J301#2.S11 (SHIELD__10), J401.A2, J401.A5, J401.A8, J401.A11, J401.A14, J401.A17, J401.A20, J401.A23, J401.A26, J401.A29, J401.A32, J401.A35, J401.A38, J401.A41, J401.A44, J401.A48, J401.B2, J401.B5, J401.B8, J401.B11, J401.B14, J401.B17, J401.B20, J401.B23, J401.B26, J401.B29, J401.B32, J401.B35, J401.B38, J401.B41, J401.B44, J401.S1 (SHIELD), J401.S2 (SHIELD__1), J501.A2, J501.A5, J501.A8, J501.A11, J501.A14, J501.A17, J501.A20, J501.A23, J501.A26, J501.A29, J501.A32, J501.A35, J501.A38, J501.A41, J501.A44, J501.A48, J501.B2, J501.B5, J501.B8, J501.B11, J501.B14, J501.B17, J501.B20, J501.B23, J501.B26, J501.B29, J501.B32, J501.B35, J501.B38, J501.B41, J501.B44, J501.S1 (SHIELD), J501.S2 (SHIELD__1), J601.A2, J601.A5, J601.A8, J601.A11, J601.A14, J601.A17, J601.A20, J601.A23, J601.A26, J601.A29, J601.A32, J601.A35, J601.A38, J601.A41, J601.A44, J601.A48, J601.B2, J601.B5, J601.B8, J601.B11, J601.B14, J601.B17, J601.B20, J601.B23, J601.B26, J601.B29, J601.B32, J601.B35, J601.B38, J601.B41, J601.B44, J601.S1 (SHIELD), J601.S2 (SHIELD__1), R101.2, R134.2, R202.1, R204.1, R206.1, R208.1, U101.AA11 (GND[267]), U101.AA22 (GND[267]), U101.AB11 (GND[267]), U101.AB12 (GND[267]), U101.AB13 (GND[267]), U101.AB14 (GND[267]), U101.AB15 (GND[267]), U101.AB16 (GND[267]), U101.AB17 (GND[267]), U101.AB18 (GND[267]), U101.AB19 (GND[267]), U101.AB20 (GND[267]), U101.AB21 (GND[267]), U101.AB22 (GND[267]), U101.AC12 (GND[267]), U101.AC13 (GND[267]), U101.AC14 (GND[267]), U101.AC15 (GND[267]), U101.AC16 (GND[267]), U101.AC17 (GND[267]), U101.AC18 (GND[267]), U101.AC19 (GND[267]), U101.AC20 (GND[267]), U101.AC21 (GND[267]), U101.AD2 (GND[267]), U101.AD5 (GND[267]), U101.AD28 (GND[267]), U101.AD31 (GND[267]), U101.AF11 (GND[267]), U101.AF12 (GND[267]), U101.AF14 (GND[267]), U101.AF15 (GND[267]), U101.AF16 (GND[267]), U101.AF17 (GND[267]), U101.AF19 (GND[267]), U101.AF20 (GND[267]), U101.AF22 (GND[267]), U101.AF23 (GND[267]), U101.AG9 (GND[267]), U101.AG11 (GND[267]), U101.AG12 (GND[267]), U101.AG14 (GND[267]), U101.AG15 (GND[267]), U101.AG16 (GND[267]), U101.AG17 (GND[267]), U101.AG19 (GND[267]), U101.AG20 (GND[267]), U101.AG22 (GND[267]), U101.AG23 (GND[267]), U101.AH2 (GND[267]), U101.AH5 (GND[267]), U101.AH7 (GND[267]), U101.AH8 (GND[267]), U101.AH9 (GND[267]), U101.AH11 (GND[267]), U101.AH12 (GND[267]), U101.AH14 (GND[267]), U101.AH15 (GND[267]), U101.AH16 (GND[267]), U101.AH17 (GND[267]), U101.AH19 (GND[267]), U101.AH20 (GND[267]), U101.AH22 (GND[267]), U101.AH23 (GND[267]), U101.AH24 (GND[267]), U101.AH25 (GND[267]), U101.AH26 (GND[267]), U101.AH29 (GND[267]), U101.AH31 (GND[267]), U101.AJ7 (GND[267]), U101.AJ8 (GND[267]), U101.AJ9 (GND[267]), U101.AJ10 (GND[267]), U101.AJ11 (GND[267]), U101.AJ12 (GND[267]), U101.AJ13 (GND[267]), U101.AJ14 (GND[267]), U101.AJ15 (GND[267]), U101.AJ16 (GND[267]), U101.AJ17 (GND[267]), U101.AJ18 (GND[267]), U101.AJ19 (GND[267]), U101.AJ20 (GND[267]), U101.AJ21 (GND[267]), U101.AJ22 (GND[267]), U101.AJ23 (GND[267]), U101.AJ24 (GND[267]), U101.AJ25 (GND[267]), U101.AJ26 (GND[267]), U101.AK4 (CFG_2), U101.AK7 (GND[267]), U101.AK8 (GND[267]), U101.AK11 (GND[267]), U101.AK14 (GND[267]), U101.AK17 (GND[267]), U101.AK20 (GND[267]), U101.AK23 (GND[267]), U101.AK26 (GND[267]), U101.AL2 (GND[267]), U101.AL5 (GND[267]), U101.AL7 (GND[267]), U101.AL8 (GND[267]), U101.AL9 (GND[267]), U101.AL11 (GND[267]), U101.AL12 (GND[267]), U101.AL14 (GND[267]), U101.AL15 (GND[267]), U101.AL17 (GND[267]), U101.AL18 (GND[267]), U101.AL20 (GND[267]), U101.AL21 (GND[267]), U101.AL23 (GND[267]), U101.AL24 (GND[267]), U101.AL26 (GND[267]), U101.AL29 (GND[267]), U101.AL31 (GND[267]), U101.AM4 (CFG_0), U101.AM7 (GND[267]), U101.AM8 (GND[267]), U101.AM9 (GND[267]), U101.AM11 (GND[267]), U101.AM12 (GND[267]), U101.AM14 (GND[267]), U101.AM15 (GND[267]), U101.AM17 (GND[267]), U101.AM18 (GND[267]), U101.AM20 (GND[267]), U101.AM21 (GND[267]), U101.AM23 (GND[267]), U101.AM24 (GND[267]), U101.AM26 (GND[267]), U101.B2 (GND[267]), U101.B5 (GND[267]), U101.B9 (GND[267]), U101.B13 (GND[267]), U101.B15 (GND[267]), U101.B18 (GND[267]), U101.B20 (GND[267]), U101.B24 (GND[267]), U101.B28 (GND[267]), U101.B31 (GND[267]), U101.E2 (GND[267]), U101.E5 (GND[267]), U101.E9 (GND[267]), U101.E13 (GND[267]), U101.E15 (GND[267]), U101.E18 (GND[267]), U101.E20 (GND[267]), U101.E24 (GND[267]), U101.E28 (GND[267]), U101.E31 (GND[267]), U101.J2 (GND[267]), U101.J5 (GND[267]), U101.J28 (GND[267]), U101.J31 (GND[267]), U101.K10 (GND[267]), U101.K11 (GND[267]), U101.K22 (GND[267]), U101.K23 (GND[267]), U101.L10 (GND[267]), U101.L11 (GND[267]), U101.L12 (GND[267]), U101.L13 (GND[267]), U101.L14 (GND[267]), U101.L15 (GND[267]), U101.L16 (GND[267]), U101.L17 (GND[267]), U101.L18 (GND[267]), U101.L19 (GND[267]), U101.L20 (GND[267]), U101.L21 (GND[267]), U101.L22 (GND[267]), U101.L23 (GND[267]), U101.M11 (GND[267]), U101.M22 (GND[267]), U101.N2 (GND[267]), U101.N5 (GND[267]), U101.N11 (GND[267]), U101.N13 (GND[267]), U101.N14 (GND[267]), U101.N15 (GND[267]), U101.N16 (GND[267]), U101.N17 (GND[267]), U101.N18 (GND[267]), U101.N19 (GND[267]), U101.N20 (GND[267]), U101.N22 (GND[267]), U101.N28 (GND[267]), U101.N31 (GND[267]), U101.P11 (GND[267]), U101.P13 (GND[267]), U101.P14 (GND[267]), U101.P15 (GND[267]), U101.P16 (GND[267]), U101.P17 (GND[267]), U101.P18 (GND[267]), U101.P19 (GND[267]), U101.P20 (GND[267]), U101.P22 (GND[267]), U101.R2 (GND[267]), U101.R5 (GND[267]), U101.R11 (GND[267]), U101.R13 (GND[267]), U101.R14 (GND[267]), U101.R15 (GND[267]), U101.R16 (GND[267]), U101.R17 (GND[267]), U101.R18 (GND[267]), U101.R19 (GND[267]), U101.R20 (GND[267]), U101.R22 (GND[267]), U101.R28 (GND[267]), U101.R31 (GND[267]), U101.T11 (GND[267]), U101.T13 (GND[267]), U101.T14 (GND[267]), U101.T15 (GND[267]), U101.T16 (GND[267]), U101.T17 (GND[267]), U101.T18 (GND[267]), U101.T19 (GND[267]), U101.T20 (GND[267]), U101.T22 (GND[267]), U101.U11 (GND[267]), U101.U13 (GND[267]), U101.U14 (GND[267]), U101.U15 (GND[267]), U101.U16 (GND[267]), U101.U17 (GND[267]), U101.U18 (GND[267]), U101.U19 (GND[267]), U101.U20 (GND[267]), U101.U22 (GND[267]), U101.V2 (GND[267]), U101.V5 (GND[267]), U101.V11 (GND[267]), U101.V13 (GND[267]), U101.V14 (GND[267]), U101.V15 (GND[267]), U101.V16 (GND[267]), U101.V17 (GND[267]), U101.V18 (GND[267]), U101.V19 (GND[267]), U101.V20 (GND[267]), U101.V22 (GND[267]), U101.V28 (GND[267]), U101.V31 (GND[267]), U101.W11 (GND[267]), U101.W13 (GND[267]), U101.W14 (GND[267]), U101.W15 (GND[267]), U101.W16 (GND[267]), U101.W17 (GND[267]), U101.W18 (GND[267]), U101.W19 (GND[267]), U101.W20 (GND[267]), U101.W22 (GND[267]), U101.Y2 (GND[267]), U101.Y11 (GND[267]), U101.Y13 (GND[267]), U101.Y14 (GND[267]), U101.Y15 (GND[267]), U101.Y16 (GND[267]), U101.Y17 (GND[267]), U101.Y18 (GND[267]), U101.Y19 (GND[267]), U101.Y20 (GND[267]), U101.Y22 (GND[267]), U101.Y31 (GND[267]), U102.3, U102.8, U103.32 (GND[4]), U103.49 (GND), U103.51 (GND), U103.57 (GND), U105.4 (GND), U105.9 (EP), U108.2 (GND), U201.2 (MODE), U201.6 (GND), U201.7 (PAD), U202.2 (MODE), U202.6 (GND), U202.7 (PAD), U203.2 (MODE), U203.6 (GND), U203.7 (PAD), U204.2 (MODE), U204.6 (GND), U204.7 (PAD), U301.11 (GND), U303.11 (GND), U305.11 (GND), U307.11 (GND), U309.11 (GND), U310.11 (GND), U311.11 (GND), U312.11 (GND), U401.11 (GND)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
unnamed: D101.2 (A), R131.2
unnamed: J101.5, R135.1
unnamed: U101.K12 (VCCIO0[4]), U101.K14 (VCCIO0[4]), U101.K15 (VCCIO0[4]), U101.K16 (VCCIO0[4])
unnamed: U101.K17 (VCCIO1[4]), U101.K18 (VCCIO1[4]), U101.K19 (VCCIO1[4]), U101.K21 (VCCIO1[4])
unnamed: U101.M23 (VCCIO2[4]), U101.P23 (VCCIO2[4]), U101.R23 (VCCIO2[4]), U101.T23 (VCCIO2[4])
unnamed: U101.AA23 (VCCIO3[4]), U101.U23 (VCCIO3[4]), U101.V23 (VCCIO3[4]), U101.W23 (VCCIO3[4])
unnamed: U101.AB23 (VCCIO4[2]), U101.AC23 (VCCIO4[2])
unnamed: U101.AA10 (VCCIO6[4]), U101.U10 (VCCIO6[4]), U101.V10 (VCCIO6[4]), U101.W10 (VCCIO6[4])
unnamed: U101.M10 (VCCIO7[4]), U101.P10 (VCCIO7[4]), U101.R10 (VCCIO7[4]), U101.T10 (VCCIO7[4])
unnamed: U101.AB10 (VCCIO8[2]), U101.AC10 (VCCIO8[2])
unnamed: C115.1, U103.16 (XI), Y101.1
unnamed: C116.1, U103.17 (XO), Y101.3
unnamed: L201.1, U201.1 (SW)
unnamed: L202.1, U202.1 (SW)
unnamed: L203.1, U203.1 (SW)
unnamed: L204.1, U204.1 (SW)
VD10: C104.1, C107.1, C108.1, C111.1, C114.1, C120.1, C121.1, U103.1 (AVDD), U103.23 (VD10[4]), U103.26 (VD10), U103.31 (DV10), U103.37 (VD10), U103.50 (VD10)
Vdrive: C207.2, C212.1, C309.1, C310.1, C311.1, C312.1, C313.1, C314.1, C315.1, C316.1, C409.1, C410.1, C411.1, C412.1, C413.1, C414.1, C415.1, C416.1, C509.1, C510.1, C511.1, C512.1, C513.1, C514.1, C515.1, C516.1, C609.1, C610.1, C611.1, C612.1, C613.1, C614.1, C615.1, C616.1, L202.2, R203.2, U301.19 (V_{CCB}), U303.19 (V_{CCB}), U305.19 (V_{CCB}), U307.19 (V_{CCB}), U309.19 (V_{CCB}), U310.19 (V_{CCB}), U311.19 (V_{CCB}), U312.19 (V_{CCB}), U401.19 (V_{CCB}), U403.19 (V_{CCB}), U405.19 (V_{CCB}), U407.19 (V_{CCB}), U409.19 (V_{CCB}), U410.19 (V_{CCB}), U411.19 (V_{CCB}), U412.19 (V_{CCB}), U501.19 (V_{CCB}), U503.19 (V_{CCB}), U505.19 (V_{CCB}), U507.19 (V_{CCB}), U509.19 (V_{CCB}), U510.19 (V_{CCB}), U511.19 (V_{CCB}), U512.19 (V_{CCB}), U601.19 (V_{CCB}), U603.19 (V_{CCB}), U605.19 (V_{CCB}), U607.19 (V_{CCB}), U609.19 (V_{CCB}), U610.19 (V_{CCB}), U611.19 (V_{CCB}), U612.19 (V_{CCB})

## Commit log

2023-09-29 First save
2023-10-06 Save
2024-02-03 Moved to PCIe connectors, added USB 3.0 Type B connector
2024-11-06 Moved to new level translator with less input current requirement
